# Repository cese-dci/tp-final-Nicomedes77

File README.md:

## Trabajo práctico final de la asignatura DCI ##
Este repositorio contiene el trabajo práctico final para la asignatura de Diseño de Circuitos Impresos de la carrera de posgrado de FIUBA.

* Autor: Nicolás Vargas Alice
* Título corto del trabajo:  Conversor DC/DC
* Descripción: Conversor DC/DC para proyectos que requieran cambios de tensiones DC en proyectos de electrónica. Placa desarrollada por la empresa Adafruit Industries.

## Licencia de este trabajo ##
Licencia: GPL 
http://www.gnu.org/licenses/gpl-3.0.html

## Estructura del TP FINAL ##

El proyecto sigue la siguiente estructura:

* doc: Toda la información sobre el circuito, principalmente de autoría o procesamiento propio. Por ejemplo:
  * Notas de ingeniería propias.
  * Notas de aplicación propias.
  * Estudios previos, estado del arte, resumen de las investigaciones.
  * Notas con cálculos.
  * Dibujos adicionales.
  * Fotos de los prototipos.
  * Presupuestos, cotizaciones.
* info: Toda la iformación recolectada, principalmente de terceros, como por ejemplo:
  * Hojas de datos.
  * Notas de aplicación.
  * Info de productos comerciales.
  * Info en internet.
* pcb: Archivos de diseño esquemático y pcb.

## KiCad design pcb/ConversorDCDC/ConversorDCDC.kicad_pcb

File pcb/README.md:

## Archivos Kicad ##

En este directorio se incluyen:

* Archivos de proyecto.
* Esquemático.
* PCB.
* Modelos  3D.
* Bibliotecas de símbolos y huellas externas (si son necesarios).

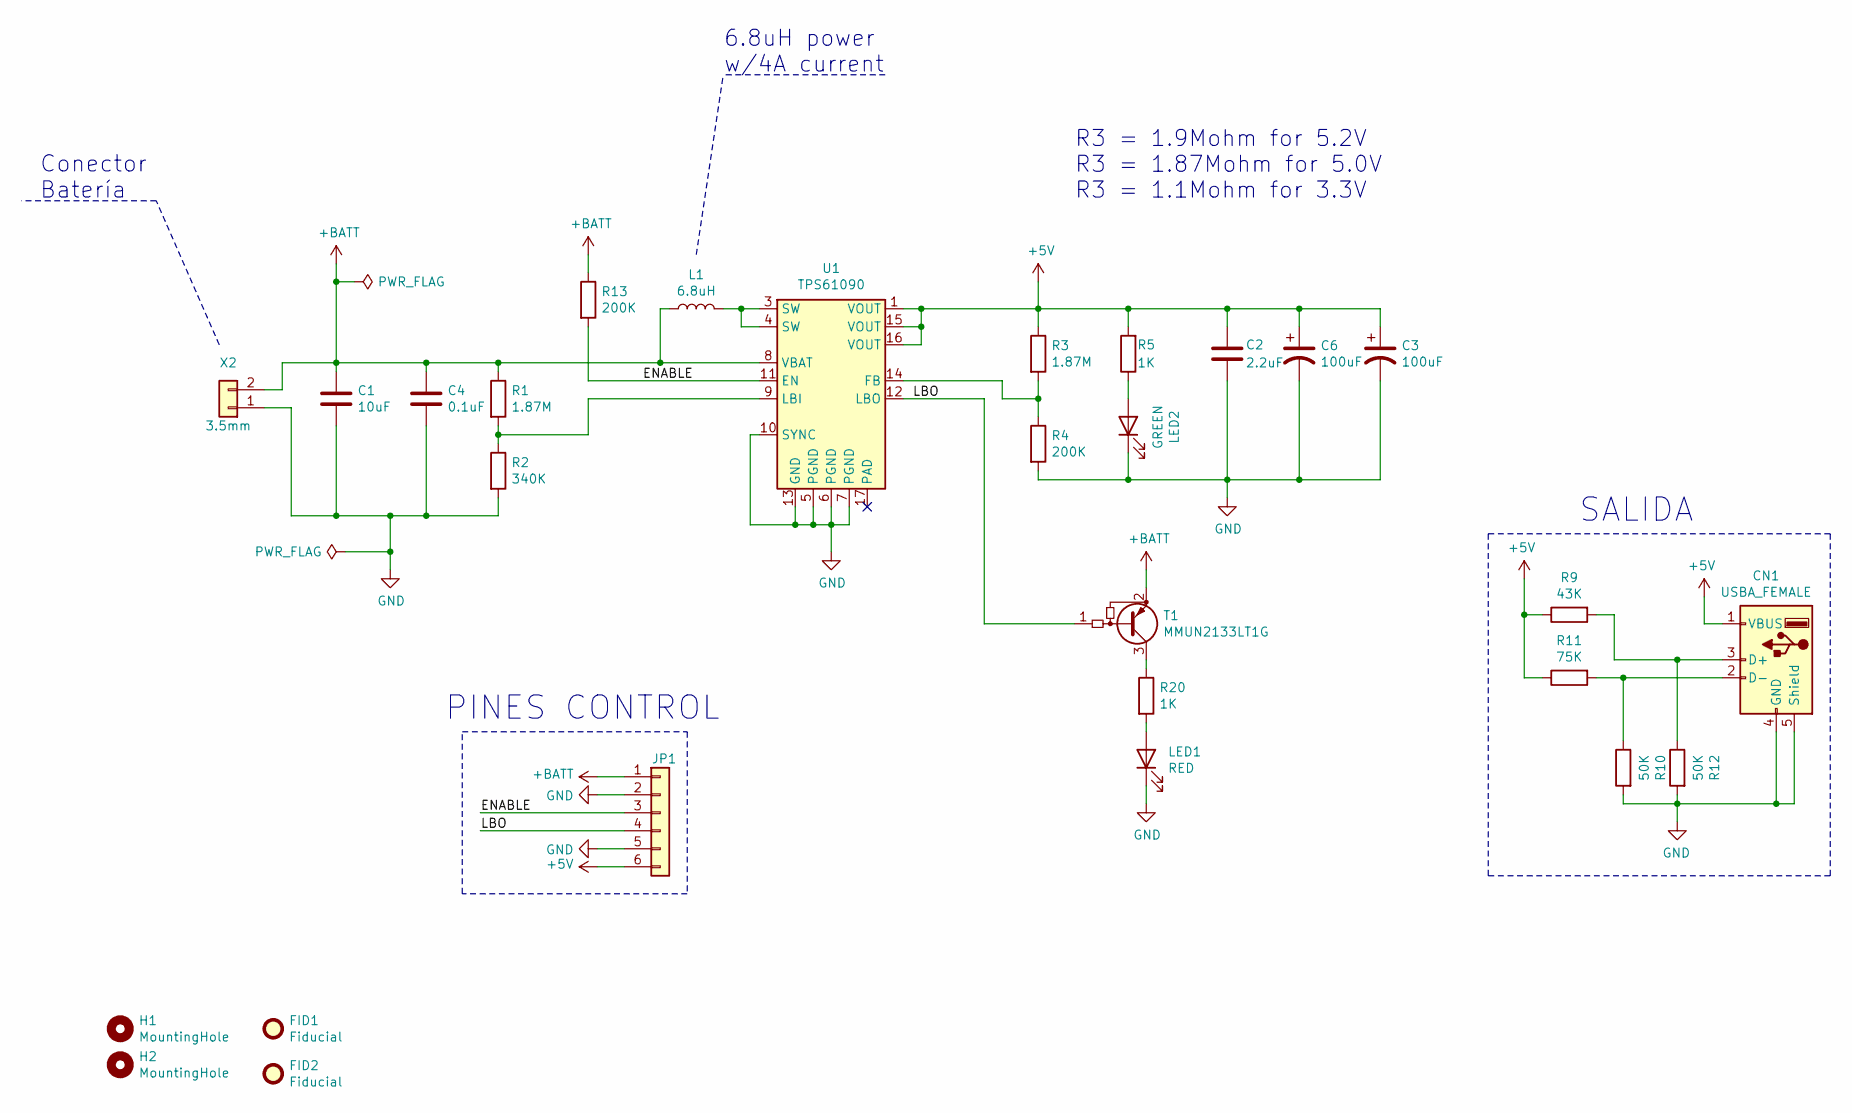
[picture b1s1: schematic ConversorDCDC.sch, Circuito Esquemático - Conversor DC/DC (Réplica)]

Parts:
C1: 10uF; C_0805_2012Metric; Digikey# 1001-2370-2-ND
C2: 2.2uF; C_0805_2012Metric; Digikey# 1001-2370-2-ND
C3, C6: 100uF; C_0805_2012Metric; Digikey# 1001-2370-2-ND
C4: 0.1uF; C_0805_2012Metric; Digikey# 1001-2370-2-ND
CN1: USBA_FEMALE; USB_A_CONNFLY_DS1095-WNR0; Mouser# 640-USB1046GF0190LBA
FID1, FID2: Fiducial; Fiducial_0.5mm_Mask1mm
H1, H2: MountingHole; MountingHole_2.2mm_M2_ISO7380_Pad_TopBottom
JP1: Conn_01x06; PinHeader_1x06_P2.54mm_Vertical
L1: 6.8uH; L_Sumida_CDMC6D28_7.25x6.5mm; Digikey# 308-1566-6-ND
LED1: RED; LED_0805_2012Metric; Mouser# 720-LYM676Q2S126Z
LED2: GREEN; LED_0805_2012Metric; Mouser# 755-SML-H12V8TT86C
R1, R3: 1.87M; R_0805_2012Metric; Digikey# 2019-RK73G2ATTD33R0FDKR-ND
R2: 340K; R_0805_2012Metric; Digikey# 2019-RK73G2ATTD33R0FDKR-ND
R4, R13: 200K; R_0805_2012Metric; Digikey# 2019-RK73G2ATTD33R0FDKR-ND
R5, R20: 1K; R_0805_2012Metric; Digikey# 2019-RK73G2ATTD33R0FDKR-ND
R9: 43K; R_0805_2012Metric; Digikey# 2019-RK73G2ATTD33R0FDKR-ND
R10, R12: 50K; R_0805_2012Metric; Digikey# 2019-RK73G2ATTD33R0FDKR-ND
R11: 75K; R_0805_2012Metric; Digikey# 2019-RK73G2ATTD33R0FDKR-ND
T1: MMUN2133LT1G; SOT-23; Digikey# MMUN2133LT1GOSTR-ND
U1: TPS61090; Texas_S-PVQFN-N16_EP2.7x2.7mm_ThermalVias; Digikey# 296-15259-2-ND
X2: 3.5mm; JST_EH_S2B-EH_1x02_P2.50mm_Horizontal; Digikey# 455-1719-ND

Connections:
+5V: C2.1, C3.1, C6.1, CN1.1 (VBUS), JP1.6, R3.1, R5.2, R9.1, R11.1, U1.1 (VOUT), U1.15 (VOUT), U1.16 (VOUT)
+BATT: C1.1, C4.1, JP1.1, L1.1, R1.1, R13.1, T1.2 (E), U1.8 (VBAT), X2.2
/ENABLE: JP1.3, R13.2, U1.11 (EN)
/LBO: JP1.4, T1.1 (B), U1.12 (LBO)
GND: C1.2, C2.2, C3.2, C4.2, C6.2, CN1.4 (GND), CN1.5 (Shield), JP1.2, JP1.5, LED1.1 (K), LED2.1 (K), R2.2, R4.2, R10.2, R12.2, U1.5 (PGND), U1.6 (PGND), U1.7 (PGND), U1.10 (SYNC), U1.13 (GND), X2.1
unnamed: CN1.2 (D-), R10.1, R11.2
unnamed: CN1.3 (D+), R9.2, R12.1
unnamed: L1.2, U1.3 (SW), U1.4 (SW)
unnamed: LED1.2 (A), R20.2
unnamed: LED2.2 (A), R5.1
unnamed: R1.2, R2.1, U1.9 (LBI)
unnamed: R3.2, R4.1, U1.14 (FB)
unnamed: R20.1, T1.3 (C)

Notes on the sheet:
R3 = 1.9Mohm for 5.2V R3 = 1.87Mohm for 5.0V R3 = 1.1Mohm for 3.3V
6.8uH power w/4A current
SALIDA
PINES CONTROL
Conector Batería

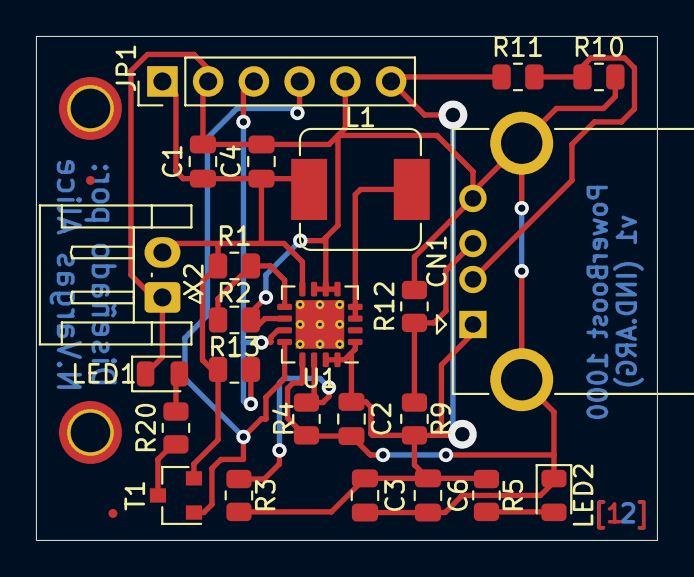
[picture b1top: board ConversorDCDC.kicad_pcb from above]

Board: 2 copper layers, 34.5 x 28.0 mm, 28 parts (0 on the bottom side), 13 nets.

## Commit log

2021-09-02 información de la propuesta
2021-09-05 esquematico hecho
2021-09-10 asociacion de huellas a simbolos
2021-09-23 entrega parcial
2021-10-13 ruteo de pcb

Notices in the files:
pcb/ConversorDCDC/ConversorDCDC.sch:
LGPL
